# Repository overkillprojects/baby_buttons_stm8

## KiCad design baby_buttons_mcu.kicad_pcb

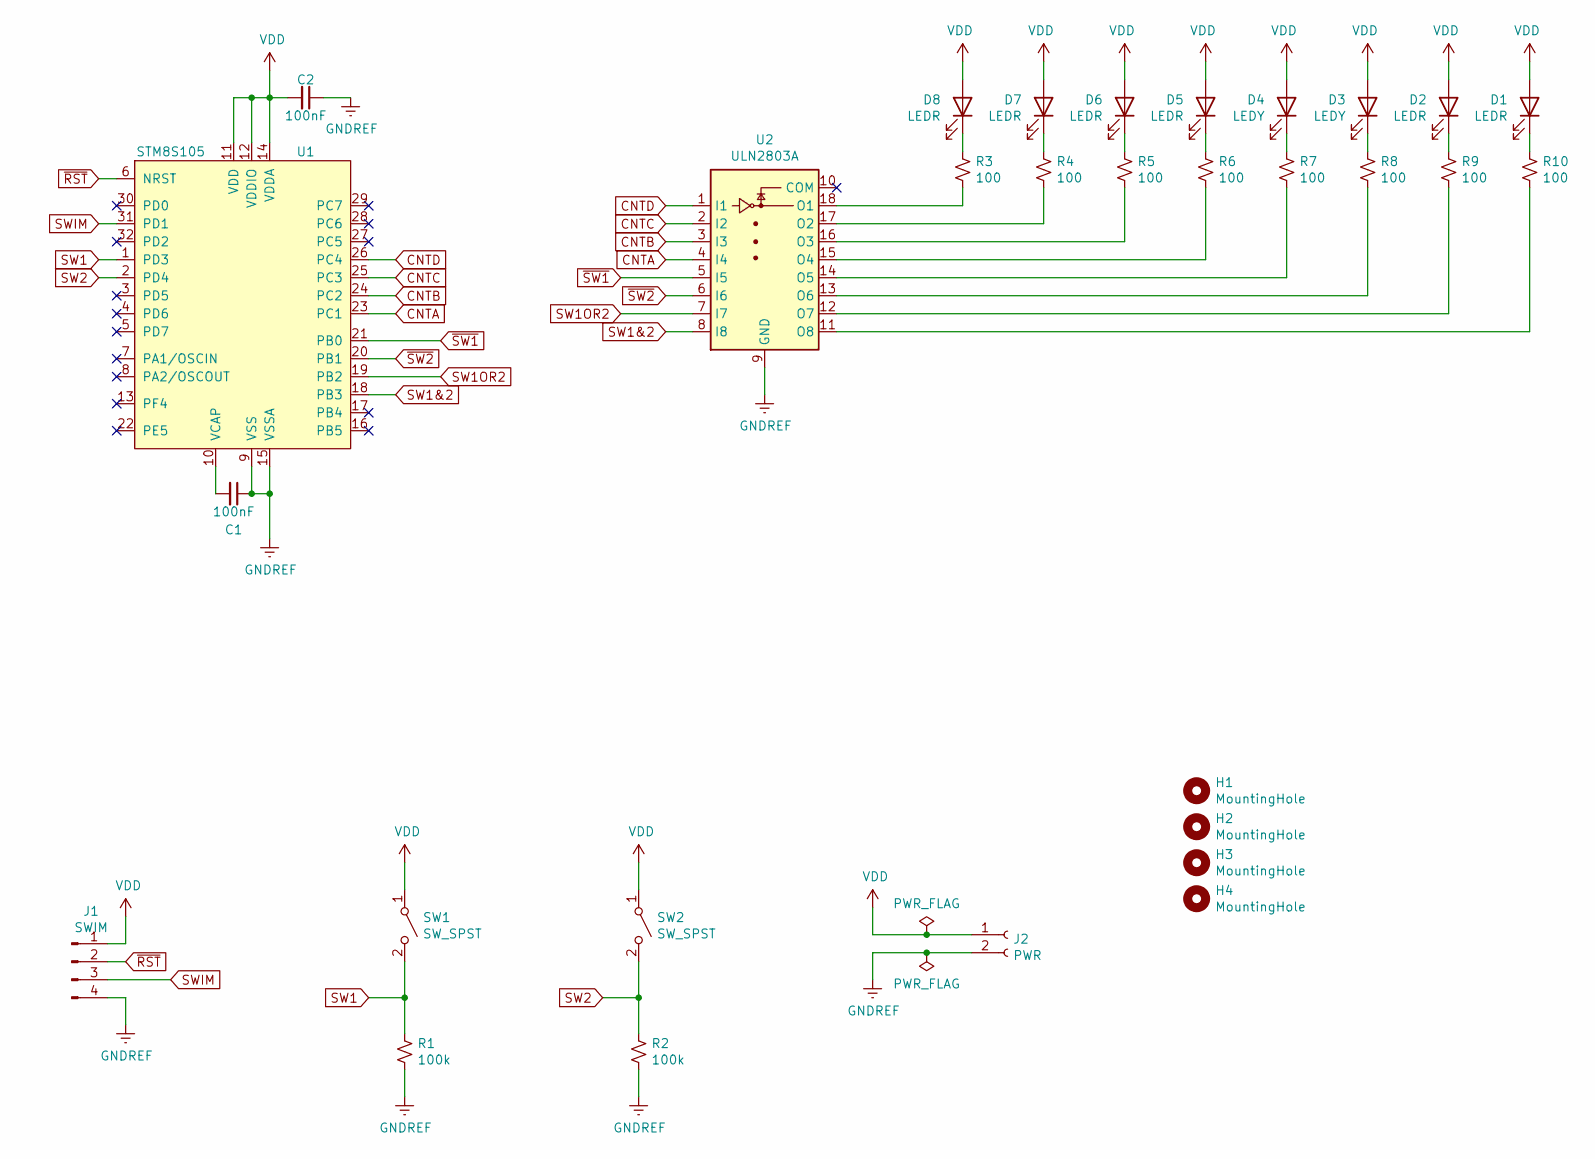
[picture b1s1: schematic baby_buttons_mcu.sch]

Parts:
C1, C2: 100nF; C_Disc_D4.7mm_W2.5mm_P5.00mm
D1, D2, D5, D6, D7, D8: LEDR; LED_D10.0mm
D3, D4: LEDY; LED_D10.0mm
H1, H2, H3, H4: MountingHole; MountingHole_2.7mm_M2.5
J1: SWIM; PinHeader_1x04_P2.54mm_Vertical
J2: PWR; PinHeader_1x02_P2.54mm_Vertical
R1, R2: 100k; R_Axial_DIN0207_L6.3mm_D2.5mm_P10.16mm_Horizontal
R3, R4, R5, R6, R7, R8, R9, R10: 100; R_Axial_DIN0207_L6.3mm_D2.5mm_P10.16mm_Horizontal
SW1, SW2: SW_SPST; PinHeader_1x02_P2.54mm_Vertical
U1: STM8S105; SDIP32-400
U2: ULN2803A; DIP-18_W7.62mm_Socket

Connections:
CNTA: U1.23 (PC1), U2.4 (I4)
CNTB: U1.24 (PC2), U2.3 (I3)
CNTC: U1.25 (PC3), U2.2 (I2)
CNTD: U1.26 (PC4), U2.1 (I1)
GNDREF: C1.1, C2.1, J1.4, J2.2, R1.2, R2.2, U1.9 (VSS), U1.15 (VSSA), U2.9 (GND)
unnamed: C1.2, U1.10 (VCAP)
unnamed: D1.1 (K), R10.1
unnamed: D2.1 (K), R9.1
unnamed: D3.1 (K), R8.1
unnamed: D4.1 (K), R7.1
unnamed: D5.1 (K), R6.1
unnamed: D6.1 (K), R5.1
unnamed: D7.1 (K), R4.1
unnamed: D8.1 (K), R3.1
unnamed: R3.2, U2.18 (O1)
unnamed: R4.2, U2.17 (O2)
unnamed: R5.2, U2.16 (O3)
unnamed: R6.2, U2.15 (O4)
unnamed: R7.2, U2.14 (O5)
unnamed: R8.2, U2.13 (O6)
unnamed: R9.2, U2.12 (O7)
unnamed: R10.2, U2.11 (O8)
SW1: R1.1, SW1.2 (B), U1.1 (PD3)
SW1&2: U1.18 (PB3), U2.8 (I8)
SW1OR2: U1.19 (PB2), U2.7 (I7)
SW2: R2.1, SW2.2 (B), U1.2 (PD4)
SWIM: J1.3, U1.31 (PD1)
VDD: C2.2, D1.2 (A), D2.2 (A), D3.2 (A), D4.2 (A), D5.2 (A), D6.2 (A), D7.2 (A), D8.2 (A), J1.1, J2.1, SW1.1 (A), SW2.1 (A), U1.11 (VDD), U1.12 (VDDIO), U1.14 (VDDA)
~RST: J1.2, U1.6 (NRST)
~SW1: U1.21 (PB0), U2.5 (I5)
~SW2: U1.20 (PB1), U2.6 (I6)

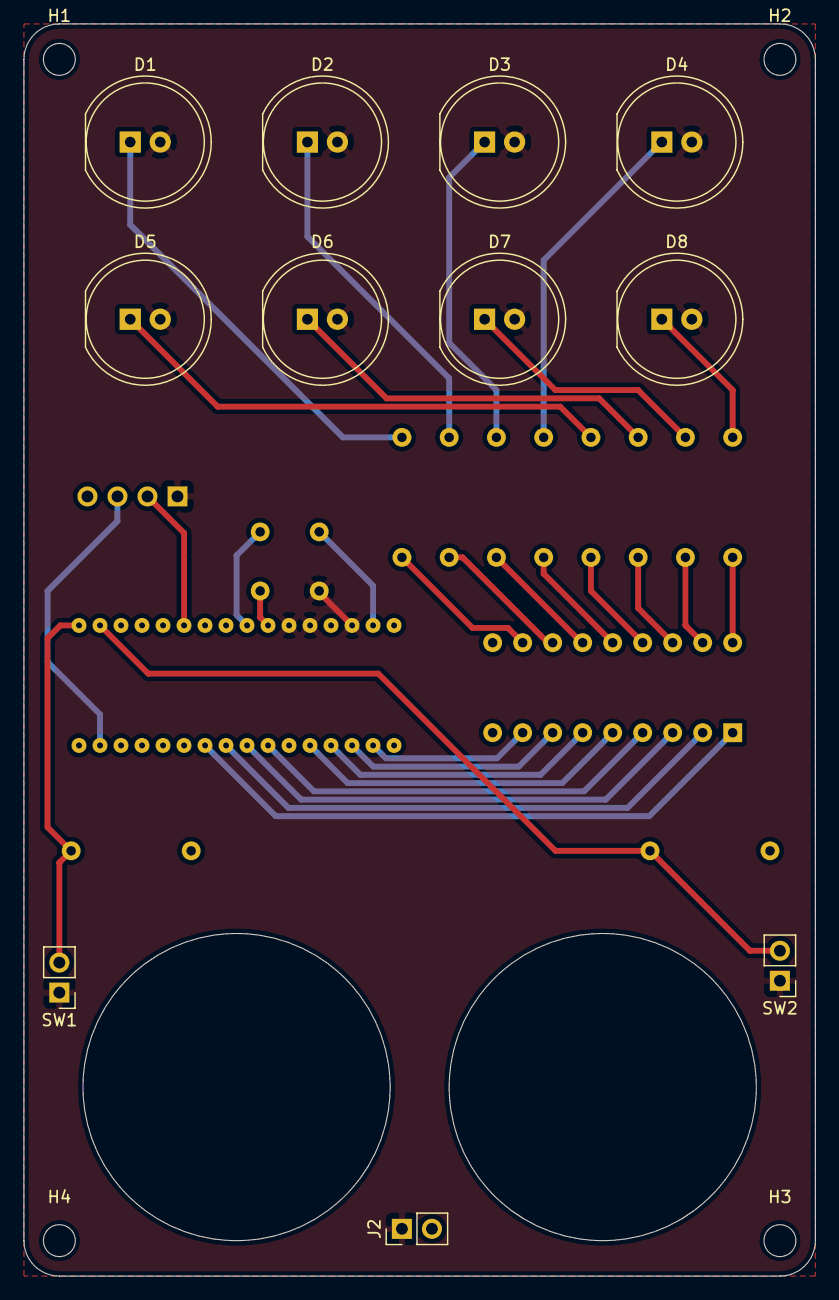
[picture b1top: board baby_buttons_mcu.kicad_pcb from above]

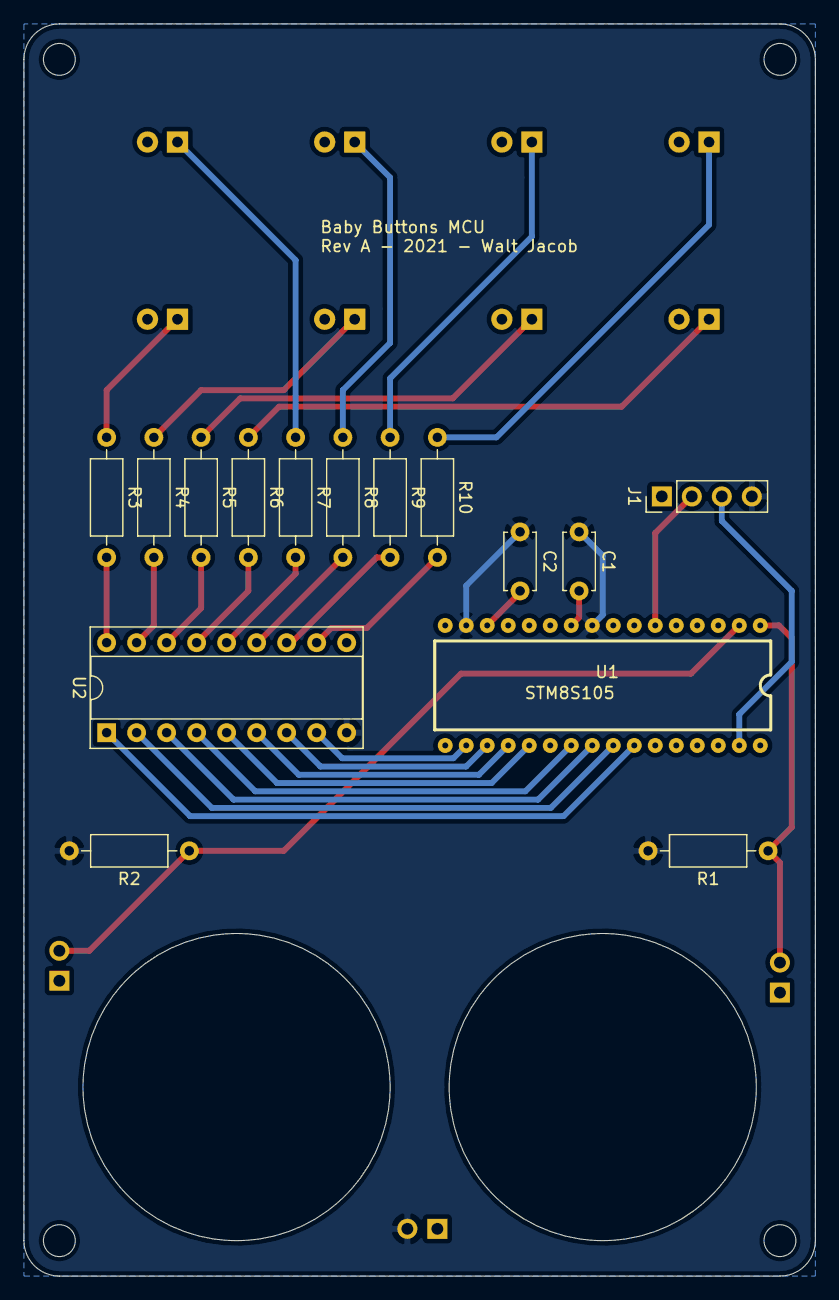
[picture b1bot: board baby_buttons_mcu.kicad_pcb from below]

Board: 2 copper layers, 67.0 x 106.0 mm, 30 parts (15 on the bottom side), 31 nets.
